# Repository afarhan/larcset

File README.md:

# larcset
LARCSet is an all analog inexpensive HF Radio.
It can be built from the pcb files of the project or ordered from hfsignals.com.
The larcset manual included here is usually dated. the latest is available from https://docs.google.com/document/d/10ynzuAaJK4nDdzysoZir7oInXb_Ld2hYF73WAQHt6xs/edit?usp=sharing

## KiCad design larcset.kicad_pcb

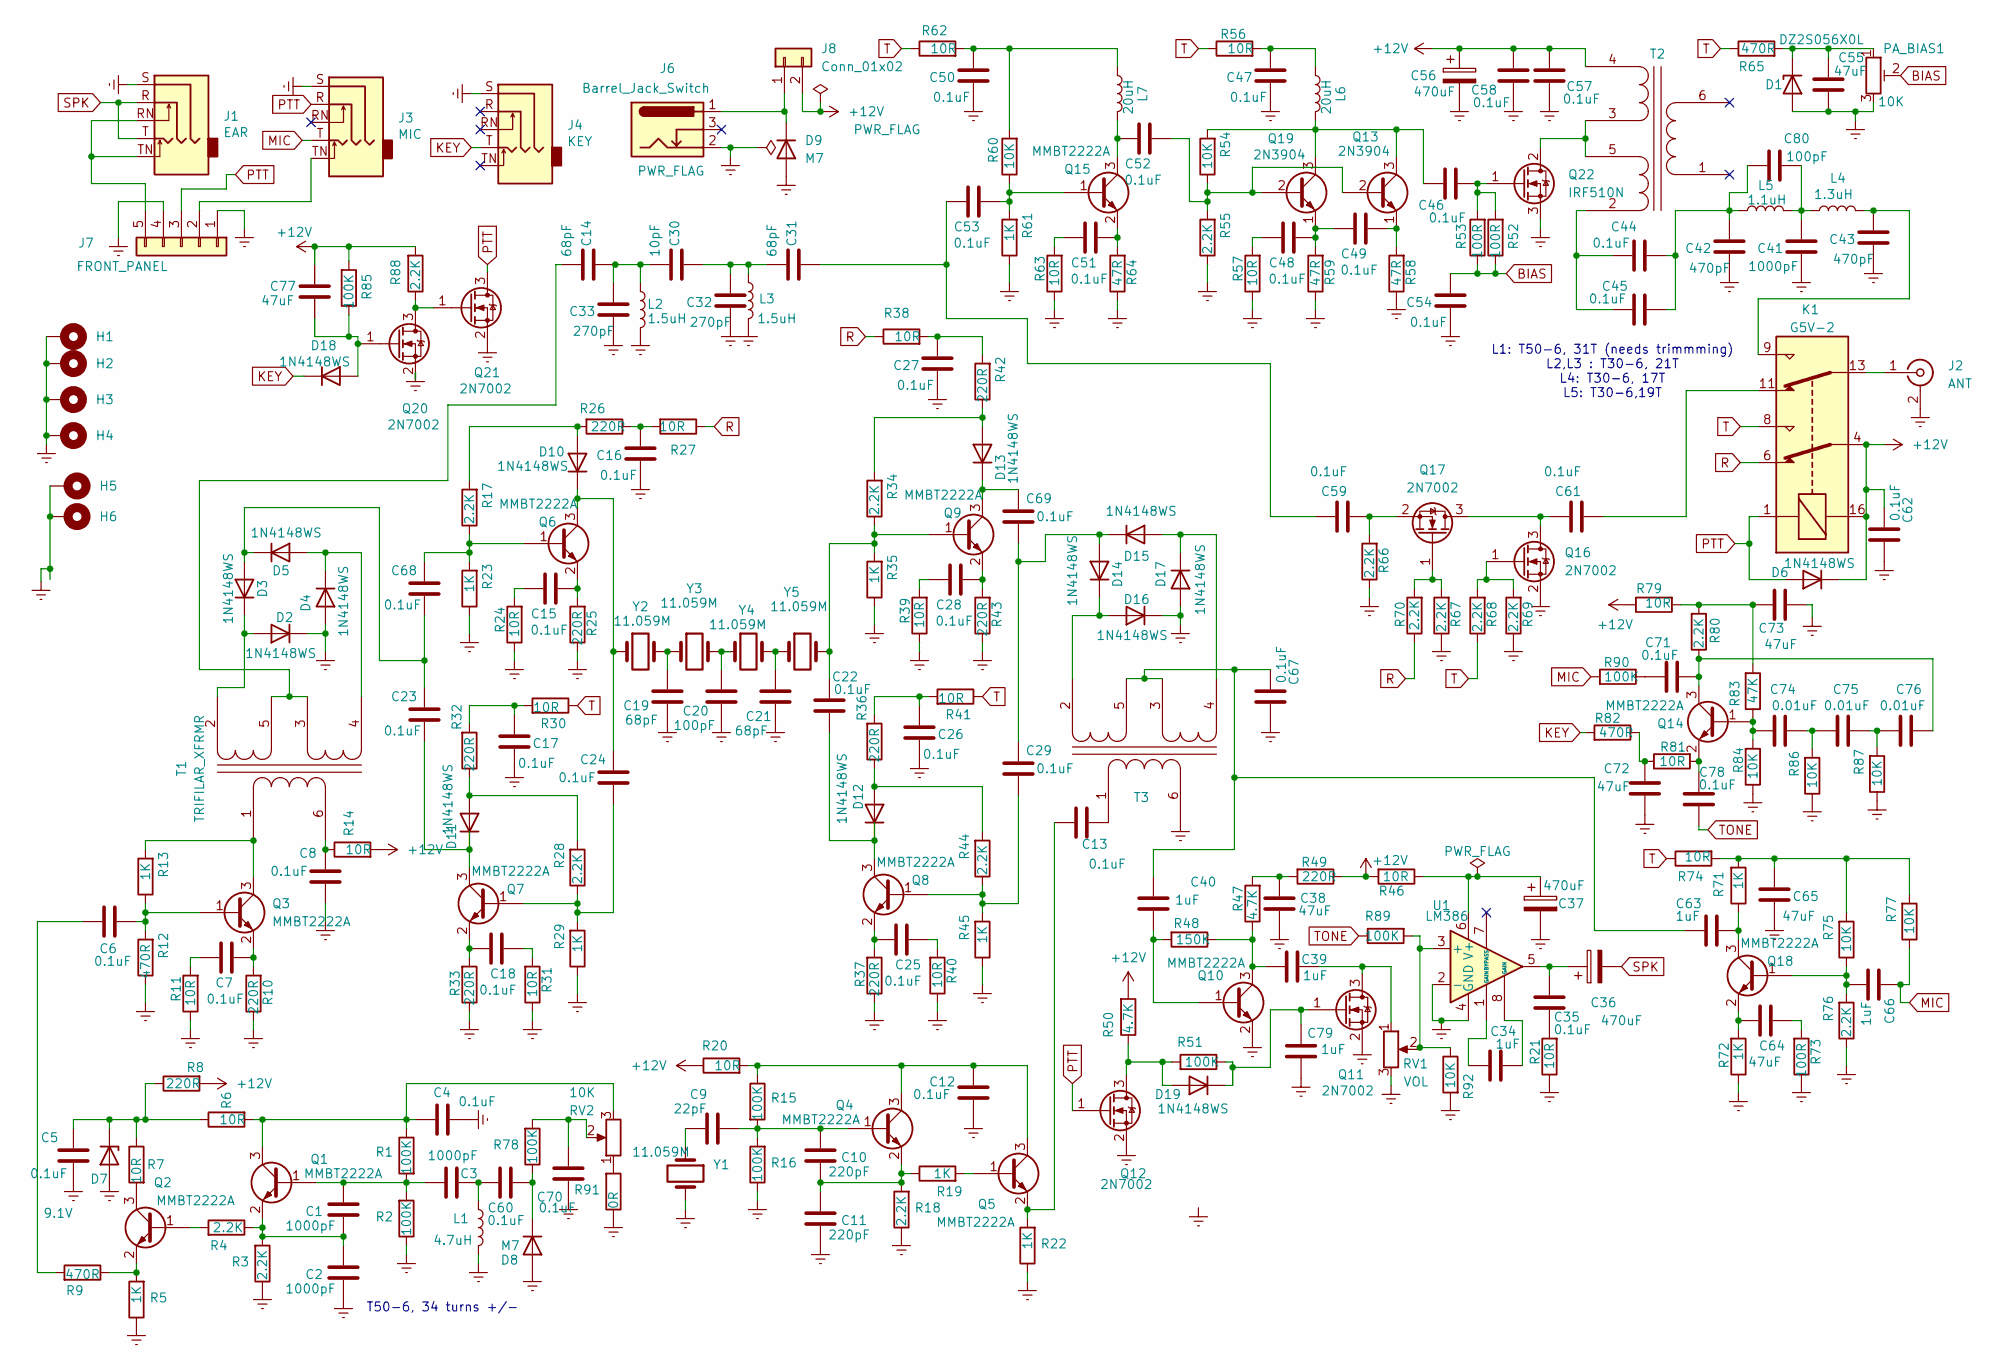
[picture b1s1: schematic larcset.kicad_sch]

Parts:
C1, C2, C3, C41: 1000pF; C_1206_3216Metric_Pad1.33x1.80mm_HandSolder
C4, C5, C6, C7, C8, C12, C13, C15, C16, C17, C18, C22, C23, C24, C25, C26, C27, C28, C29, C35, C44, C45, C46, C47, C48, C49, C50, C51, C52, C53, C54, C57, C58, C59, C60, C61, C62, C67, C68, C69, C70, C71, C78: 0.1uF; C_1206_3216Metric_Pad1.33x1.80mm_HandSolder
C9: 22pF; C_1206_3216Metric_Pad1.33x1.80mm_HandSolder
C10, C11: 220pF; C_1206_3216Metric_Pad1.33x1.80mm_HandSolder
C14, C19, C21, C31: 68pF; C_1206_3216Metric_Pad1.33x1.80mm_HandSolder
C20, C80: 100pF; C_1206_3216Metric_Pad1.33x1.80mm_HandSolder
C30: 10pF; C_1206_3216Metric_Pad1.33x1.80mm_HandSolder
C32, C33: 270pF; C_1206_3216Metric_Pad1.33x1.80mm_HandSolder
C34, C39, C40, C63, C66, C79: 1uF; C_1206_3216Metric_Pad1.33x1.80mm_HandSolder
C36, C37, C56: 470uF; C_Elec_8x10.2
C38, C55, C64, C65, C72, C73, C77: 47uF; C_1206_3216Metric_Pad1.33x1.80mm_HandSolder
C42, C43: 470pF; C_1206_3216Metric_Pad1.33x1.80mm_HandSolder
C74, C75, C76: 0.01uF; C_1206_3216Metric_Pad1.33x1.80mm_HandSolder
D1: DZ2S056X0L; D_SOD-523
D2, D3, D4, D5, D6, D10, D11, D12, D13, D14, D15, D16, D17, D18, D19: 1N4148WS; D_SOD-323
D7: 9.1V; D_SOD-523
D8, D9: M7; D_SMA
H1, H2, H3, H4, H5, H6: MountingHole_Pad; MountingHole_3.2mm_M3_DIN965_Pad
J1: EAR; Jack_3.5mm_Ledino_KB3SPRS_Horizontal
J2: ANT; BNC_Amphenol_B6252HB-NPP3G-50_Horizontal
J3: MIC; Jack_3.5mm_Ledino_KB3SPRS_Horizontal
J4: KEY; Jack_3.5mm_Ledino_KB3SPRS_Horizontal
J6: Barrel_Jack_Switch; BarrelJack_Horizontal
J7: FRONT_PANEL; PinHeader_1x05_P2.54mm_Vertical
J8: Conn_01x02; PinHeader_1x02_P2.54mm_Vertical
K1: G5V-2; Relay_DPDT_Omron_G5V-2
L1: 4.7uH; L_Axial_L7.0mm_D3.3mm_P5.08mm_Vertical_Fastron_MICC
L2, L3: 1.5uH; L_Axial_L7.0mm_D3.3mm_P5.08mm_Vertical_Fastron_MICC
L4: 1.3uH; L_Axial_L7.0mm_D3.3mm_P5.08mm_Vertical_Fastron_MICC
L5: 1.1uH; L_Axial_L7.0mm_D3.3mm_P5.08mm_Vertical_Fastron_MICC
L6, L7: 20uH; L_Axial_L7.0mm_D3.3mm_P5.08mm_Vertical_Fastron_MICC
PA_BIAS1: 10K; Potentiometer_Bourns_3386P_Vertical
Q1, Q2, Q3, Q4, Q5, Q6, Q7, Q8, Q9, Q10, Q14, Q15, Q18: MMBT2222A; SOT-23
Q11, Q12, Q16, Q17, Q20, Q21: 2N7002; SOT-23
Q13, Q19: 2N3904; TO-92_Inline_Wide
Q22: IRF510N; TO-220-3_Vertical
R1, R2, R15, R16, R51, R78, R85, R89, R90: 100K; R_1206_3216Metric_Pad1.30x1.75mm_HandSolder
R3, R4, R17, R18, R28, R34, R44, R55, R66, R67, R68, R69, R70, R76, R80, R88: 2.2K; R_1206_3216Metric_Pad1.30x1.75mm_HandSolder
R5, R13, R19, R22, R23, R29, R35, R45, R61, R71, R72: 1K; R_1206_3216Metric_Pad1.30x1.75mm_HandSolder
R6, R7, R11, R14, R20, R21, R24, R27, R30, R31, R38, R39, R40, R41, R46, R56, R57, R62, R63, R74, R79, R81: 10R; R_1206_3216Metric_Pad1.30x1.75mm_HandSolder
R8, R10, R25, R26, R32, R33, R36, R37, R42, R43, R49: 220R; R_1206_3216Metric_Pad1.30x1.75mm_HandSolder
R9, R12, R65, R82: 470R; R_1206_3216Metric_Pad1.30x1.75mm_HandSolder
R47, R50: 4.7K; R_1206_3216Metric_Pad1.30x1.75mm_HandSolder
R48: 150K; R_1206_3216Metric_Pad1.30x1.75mm_HandSolder
R52, R53, R73: 100R; R_1206_3216Metric_Pad1.30x1.75mm_HandSolder
R54, R60, R75, R77, R84, R86, R87, R92: 10K; R_1206_3216Metric_Pad1.30x1.75mm_HandSolder
R58, R59, R64: 47R; R_1206_3216Metric_Pad1.30x1.75mm_HandSolder
R83: 47K; R_1206_3216Metric_Pad1.30x1.75mm_HandSolder
R91: 0R; R_1206_3216Metric_Pad1.30x1.75mm_HandSolder
RV1: VOL; Potentiometer_Alps_RK163_Single_Horizontal
RV2: 10K; Potentiometer_Alps_RK163_Single_Horizontal
T1, T2, T3: TRIFILAR_XFRMR; DIP-6_W7.62mm
U1: LM386; SOIC-8_3.9x4.9mm_P1.27mm
Y1, Y2, Y3, Y4, Y5: 11.059M; Crystal_HC49-U_Vertical

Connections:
+12V: C56.1, C57.1, C58.1, C62.1, C77.1, D6.1 (K), J8.2, K1.4, K1.16, R8.2, R14.2, R20.1, R46.2, R49.1, R50.2, R79.1, R85.2, R88.2, T2.4 (SD)
BIAS: C54.1, PA_BIAS1.2, R52.1, R53.1
Earth: C2.2, C4.2, C5.2, C8.2, C11.2, C12.2, C16.2, C17.2, C19.2, C20.2, C21.2, C26.2, C27.2, C32.2, C33.2, C37.2, C38.2, C41.2, C42.2, C43.2, C47.2, C50.2, C54.2, C55.2, C56.2, C57.2, C58.2, C62.2, C65.2, C67.2, C70.1, C72.2, C73.2, C79.1, D1.2 (A), D2.1 (K), D4.2 (A), D7.2 (A), D8.2 (A), D9.2 (A), D16.1 (K), D17.2 (A), H1.1, H2.1, H3.1, H4.1, H5.1, H6.1, J1.S, J2.2 (Ext), J3.S, J4.S, J6.2, J7.1, J7.4, L1.1, L2.1, L3.1, PA_BIAS1.3, Q10.2 (E), Q11.2 (S), Q12.2 (S), Q16.2 (S), Q20.2 (S), Q21.2 (S), Q22.3 (S), R2.1, R3.1, R5.1, R10.1, R11.1, R12.1, R16.1, R18.1, R21.1, R22.1, R23.1, R24.1, R25.1, R29.1, R31.1, R33.1, R35.1, R37.1, R39.1, R40.1, R43.1, R45.1, R55.1, R57.1, R58.1, R59.1, R61.1, R63.1, R64.1, R66.1, R67.1, R69.1, R72.1, R73.1, R76.1, R84.1, R86.1, R87.1, R91.1, R92.2, RV1.3, T3.6 (AB), U1.2 (-), U1.4 (GND), Y1.2
KEY: D18.1 (K), J4.T, R82.2
MIC: C66.1, J3.T, R77.1, R90.2
unnamed: C3.2, C60.1, L1.2
unnamed: C6.2, R9.2
unnamed: C7.1, R11.2
unnamed: C9.2, Y1.1
unnamed: C14.1, C30.2, C33.1, L2.2
unnamed: C15.1, R24.2
unnamed: C16.1, R26.1, R27.2
unnamed: C17.1, R30.2, R32.2
unnamed: C18.1, R31.2
unnamed: C19.1, Y2.2, Y3.1
unnamed: C20.1, Y3.2, Y4.1
unnamed: C21.1, Y4.2, Y5.1
unnamed: C25.1, R40.2
unnamed: C26.1, R36.2, R41.2
unnamed: C27.1, R38.2, R42.2
unnamed: C28.1, R39.2
unnamed: C30.1, C31.2, C32.1, L3.2
unnamed: C31.1, C53.1, C59.1
unnamed: C34.1, U1.1 (GAIN)
unnamed: C34.2, U1.8 (GAIN)
unnamed: C35.1, C36.1, U1.5
unnamed: C35.2, R21.2
unnamed: C38.1, R47.2, R49.2
unnamed: C47.1, L6.2, R56.2
unnamed: C48.1, R57.2
unnamed: C50.1, L7.2, R60.2, R62.2
unnamed: C51.1, R63.2
unnamed: C61.2, K1.11
unnamed: C64.1, R73.2
unnamed: C65.1, R71.2, R74.2, R75.2, R77.2
unnamed: C70.2, R78.2, RV2.2
unnamed: C71.1, R90.1
unnamed: C72.1, R81.1, R82.1
unnamed: C73.1, R79.2, R80.2, R83.2
unnamed: C74.1, C75.2, R86.2
unnamed: C75.1, C76.2, R87.2
unnamed: C55.1, D1.1 (K), PA_BIAS1.1, R65.2
unnamed: D2.2 (A), D3.1 (K), T1.2 (SA)
unnamed: C23.1, C68.2, D3.2 (A), D5.1 (K)
unnamed: D4.1 (K), D5.2 (A), T1.4 (SD)
unnamed: C5.1, D7.1 (K), R6.1, R7.1, R8.1
unnamed: C60.2, D8.1 (K), R78.1
unnamed: D9.1 (K), J6.1, J8.1
unnamed: D10.2 (A), R17.2, R26.2
unnamed: C24.1, D10.1 (K), Q6.3 (C), Y2.1
unnamed: D11.2 (A), R28.2, R32.1
unnamed: C23.2, D11.1 (K), Q7.3 (C)
unnamed: D12.2 (A), R36.1, R44.2
unnamed: C22.2, D12.1 (K), Q8.3 (C)
unnamed: D13.2 (A), R34.2, R42.1
unnamed: C69.1, D13.1 (K), Q9.3 (C)
unnamed: C29.1, C69.2, D14.2 (A), D15.1 (K)
unnamed: D14.1 (K), D16.2 (A), T3.2 (SA)
unnamed: D15.2 (A), D17.1 (K), T3.4 (SD)
unnamed: C77.2, D18.2 (A), Q20.1 (G), R85.1
unnamed: D19.2 (A), Q12.3 (D), R50.1, R51.2
unnamed: C79.2, D19.1 (K), Q11.1 (G), R51.1
unnamed: J2.1 (In), K1.13
unnamed: J3.TN, J7.2
unnamed: J1.RN, J1.TN, J7.5
unnamed: C1.1, C3.1, Q1.1 (B), R1.2, R2.2
unnamed: C4.1, Q1.3 (C), R1.1, R6.2, RV2.3
unnamed: C1.2, C2.1, Q1.2 (E), R3.2, R4.1
unnamed: Q2.1 (B), R4.2
unnamed: Q2.3 (C), R7.2
unnamed: Q2.2 (E), R5.2, R9.1
unnamed: C6.1, Q3.1 (B), R12.2, R13.1
unnamed: Q3.3 (C), R13.2, T1.1 (AA)
unnamed: C7.2, Q3.2 (E), R10.2
unnamed: C9.1, C10.1, Q4.1 (B), R15.2, R16.2
unnamed: C12.1, Q4.3 (C), Q5.3 (C), R15.1, R20.2
unnamed: C10.2, C11.1, Q4.2 (E), R18.2, R19.1
unnamed: Q5.1 (B), R19.2
unnamed: C13.1, Q5.2 (E), R22.2
unnamed: C68.1, Q6.1 (B), R17.1, R23.2
unnamed: C15.2, Q6.2 (E), R25.2
unnamed: C24.2, Q7.1 (B), R28.1, R29.2
unnamed: C18.2, Q7.2 (E), R33.2
unnamed: C29.2, Q8.1 (B), R44.1, R45.2
unnamed: C25.2, Q8.2 (E), R37.2
unnamed: C22.1, Q9.1 (B), R34.1, R35.2, Y5.2
unnamed: C28.2, Q9.2 (E), R43.2
unnamed: C40.1, Q10.1 (B), R48.2
unnamed: C39.1, Q10.3 (C), R47.1, R48.1
unnamed: C39.2, Q11.3 (D), RV1.1
unnamed: C52.2, Q13.2 (B), Q19.2 (B), R54.1, R55.2
unnamed: C46.1, L6.1, Q13.3 (C), Q19.3 (C), R54.2
unnamed: C49.2, Q13.1 (E), R58.2
unnamed: C74.2, Q14.1 (B), R83.1, R84.2
unnamed: C71.2, C76.1, Q14.3 (C), R80.1
unnamed: C78.2, Q14.2 (E), R81.2
unnamed: C53.2, Q15.1 (B), R60.1, R61.2
unnamed: C52.1, L7.1, Q15.3 (C)
unnamed: C51.2, Q15.2 (E), R64.2
unnamed: C61.1, Q16.3 (D), Q17.3 (D)
unnamed: Q16.1 (G), R68.2, R69.2
unnamed: Q17.1 (G), R67.2, R70.2
unnamed: C59.2, Q17.2 (S), R66.2
unnamed: C66.2, Q18.1 (B), R75.1, R76.2
unnamed: C63.2, Q18.3 (C), R71.1
unnamed: C64.2, Q18.2 (E), R72.2
unnamed: C48.2, C49.1, Q19.1 (E), R59.2
unnamed: Q20.3 (D), Q21.1 (G), R88.1
unnamed: Q22.2 (D), T2.3 (SC), T2.5 (SB)
unnamed: C46.2, Q22.1 (G), R52.2, R53.2
unnamed: R91.2, RV2.1
unnamed: C8.1, R14.1, T1.6 (AB)
unnamed: C14.2, T1.3 (SC), T1.5 (SB)
unnamed: C44.1, C45.1, T2.2 (SA)
unnamed: C13.2, T3.1 (AA)
unnamed: C40.2, C63.1, C67.1, T3.3 (SC), T3.5 (SB)
unnamed: R89.2, R92.1, RV1.2, U1.3 (+)
unnamed: C37.1, R46.1, U1.6 (V+)
PTT: D6.2 (A), J3.R, J7.3, K1.1, Q12.1 (G), Q21.3 (D)
R: K1.6, R27.1, R38.1, R70.1
SPK: C36.2, J1.R, J1.T
T: K1.8, R30.1, R41.1, R56.1, R62.1, R65.1, R68.1, R74.1
TONE: C78.1, R89.1

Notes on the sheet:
T50-6, 34 turns +/-
L1: T50-6, 31T (needs trimmming) L2,L3 : T30-6, 21T L4: T30-6, 17T L5: T30-6,19T

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
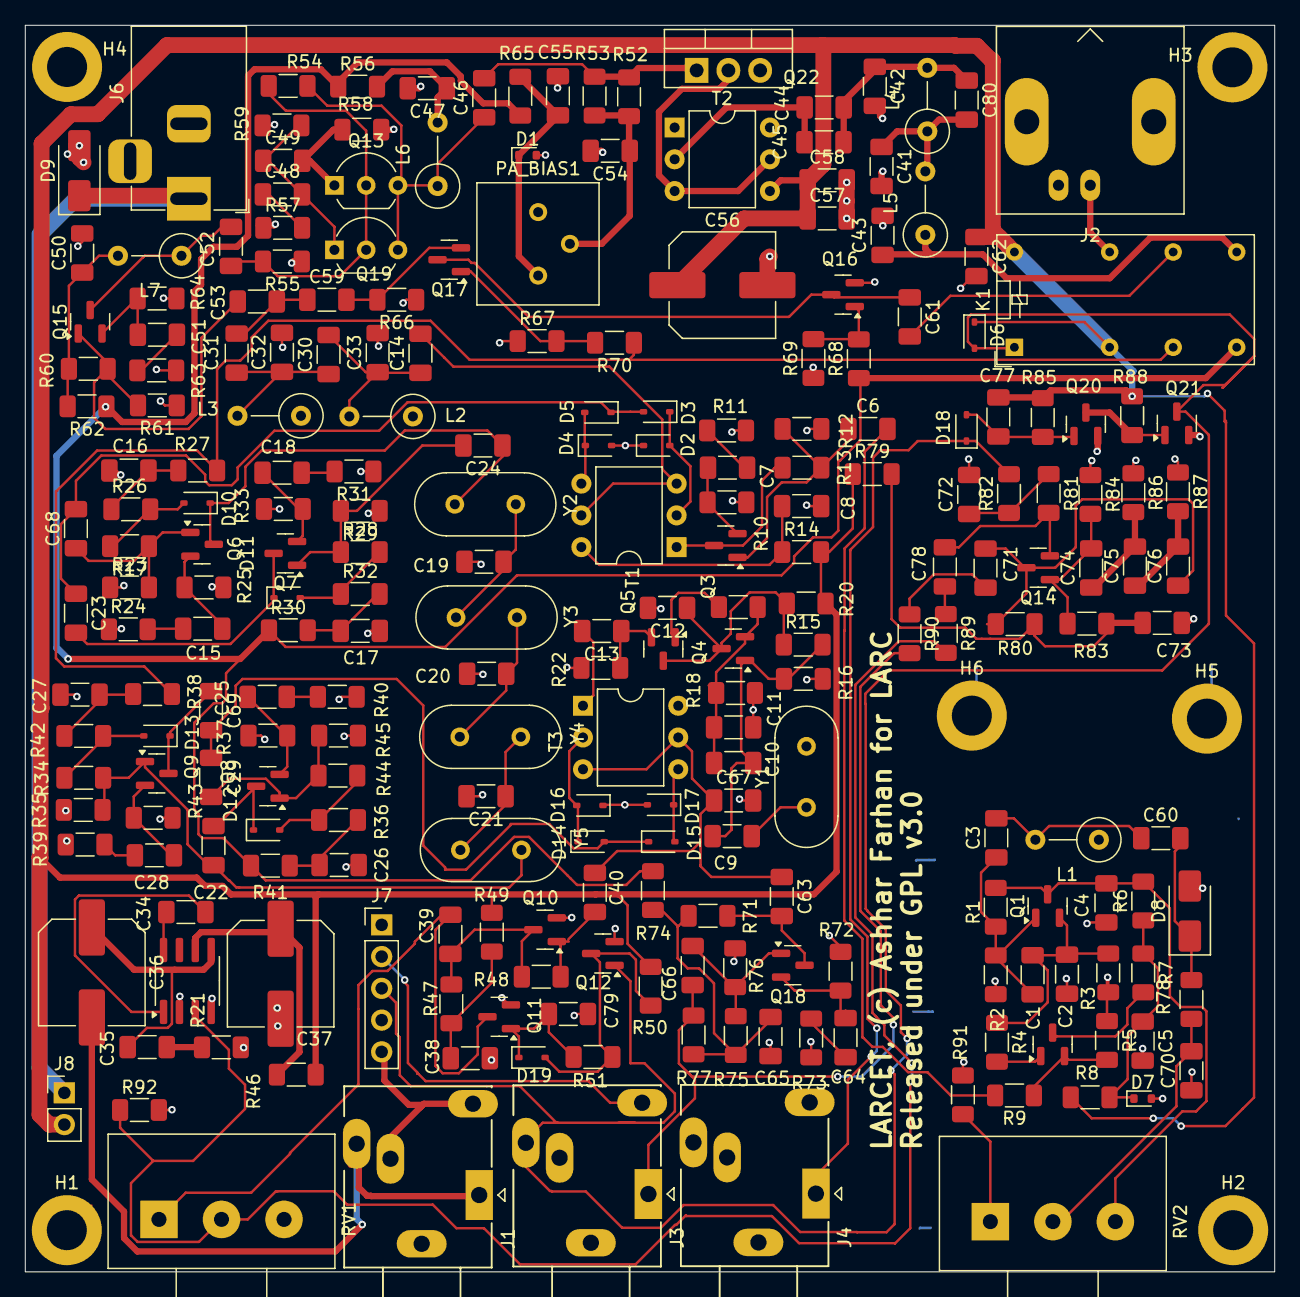
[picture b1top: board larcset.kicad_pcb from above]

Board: 2 copper layers, 99.9 x 99.7 mm, 246 parts (0 on the bottom side), 126 nets.

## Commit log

2025-12-04 Launchset
    Files of the schematic, pcb layout and the manual are added
2025-12-18 Updated inductor values
2026-01-11 Added schematic pdf
2026-01-11 Update README with build and ordering details
    Added additional information about building and ordering LARCSet.

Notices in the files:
larcset.kicad_pcb:
Released under GPL v3.0
